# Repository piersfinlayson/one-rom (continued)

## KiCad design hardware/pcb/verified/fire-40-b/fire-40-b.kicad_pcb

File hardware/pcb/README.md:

# PCB Files

Contains One ROM PCB design files, organised into:

- [`verified/`](verified/README.md) - Verified designs that have been tested and work.
- [`unverified/`](unverified/README.md) - Unverified designs that have not been tested.
- [`3dmodels/`](3dmodels/) - 3D models of parts with no standard kicad model of their own.
- [`scripts/`](scripts/) - Scripts that build models and render the PCBs.

Before using any of the designs, review the hardware [LICENSE](/LICENSE.md#cern-ohl-w-20-license) and [NOTICE](/hardware/NOTICE) files.

## Recommended Revisions

Last Updated 8th September 2026.

The following table lists the recommended verified designs.  Each design has been manufactured and assembled using JLCPCB's PCB assembly service, and verified to work correctly.

| Model | MCU | Pins | USB | SWD | Image Select Pins | X Pins | RGB | PCB |
|-------|-----|------|-----|-----|-------------------|--------|-----|-------|
| Fire  | RP2354A | 24 | C | ✓ | 4 | 2 | ✓ | [fire-24-f](./verified/fire-24-f/README.md) |
| Fire  | RP2354A | 24 | C (upright) | ✓ | 4 | 2 | ✓ | [fire-24-g](./verified/fire-24-g/README.md) |
| Fire  | RP2354B | 28 | C | ✓ | 4 | 2 | ✓ | [fire-28-c](./verified/fire-28-c/README.md) |
| Fire  | RP2354B | 28 | C (upright) | ✓ | 4 | 2 | ✓ | [fire-28-d](./verified/fire-28-d/README.md) |
| Fire  | RP2354B | 32 | C | ✓ | 4 | n/a | ✓ | [fire-32-b2](./verified/fire-32-b2/README.md) |
| Fire  | RP2354B | 32 | C (upright) | ✓ | 4 | n/a | ✓ | [fire-32-c](./verified/fire-32-c/README.md) |
| Fire  | RP2354B | 40 | C | ✓ | 4 | n/a | ✓ | [fire-40-b](./verified/fire-40-b/README.md) |
| Fire  | RP2354B | 40 | C (upright) | ✓ | 4 | n/a | ✓ | [fire-40-c](./verified/fire-40-c/README.md) |

**One ROM 28C onwards, 32 and 40 require components on the top and bottom of the PCB**

To identify a board or see it looks like see [onerom.org/identify/](https://onerom.org/identify/).

There may be later, unverified, revisions not in the list above.  These may have improvements over the recommended revisions, but they have not been verified to work.  If you want to use one of these later revisions, read the relevant README before ordering.

## Alternative Components

Sometimes your PCB manufacturer/assembler may be out of stock of a particular component.  This section lists some reasonable alternatives, using LCSC/JLC part numbers.

| Original Component | Original LCSC/JLC Part Number | Alternative Component | Alternative LCSC/JLC Part Number | Verified? | Notes |
|-|-|-|-|-|-|
| Diodes Inc AP2112K-3.3TRG1 | C51118 | Tech Public AP2112K-3.3TRG1 | C23380830 | Yes | Jelly bean part, same specs |
| Uniroyal 0201WMF1002TEE | C473048 | Yageo RC0201FR-0710KL | C106225 | No | Jelly bean part, same specs |
| Samsung CL03A104KO3NNNC | C307380 | Murata GRM033Z71C104KE14D | C668346 | Yes | 0.1uF decoupler.  X7R rather than X5R - this is the part used on all boards fabbed to date. |

The RP2354B can be replaced with the RP2350B _if the design supports external flash and it is populated with the correct resistors present/missing_.

Some designs, such as fire-40-c, have hardware support for both external flash plus an RP2354B, so two lots of flash.  Fabricating this option requires the correct 0R resistors to be populated/not populated.  See the board schematic for more details.

**The external flash option has not been tested on the current recommended designs.**

In some cases, alternative BOM/POS files are already provided for some alternative components.  In other cases, you may need to edit the BOM/POS files yourself to substitute the alternative component.  _Always_ double check component values, part numbers and placement before ordering.

## Notes on Fabrication

All recommended designs have been manufactured and assembled using JLCPCB's PCB assembly service.  The gerbers and BOM/POS files in each revision's `fab/` directory are compatible with JLCPCB's requirements.

Some variants offer multiple sets of BOM/POS files or different combinations of components.  Read the relevant revision's README for details.

You need to exercise care when submitting the order to ensure the correct options are selected.  In particular:

- Select economic assembly, not standard assembly, for cost reasons, if available for your choice of board.
- Use standard 1.6mm PCB thickness.  You probably want HASL with lead finish for cost reasons.
- You have to select the desired PCB colour as part of the PCB ordering process.  Red is recommended for Fire and blue for Ice.
- As of late 2025 you no longer need to remove JLC's order ID from the PCBs, but it is worth checking this is still the case when you place your order.
- When selecting assembly choose either top or top + bottom depending on whether your chosen design has parts on the bottom.
- After uploading the BOM and position files for assembly, you need to ensure all parts are available and checked.
- You must ensure JLC is showing the correct orientation for all components.  There are silkscreen markings for pin 1 on all ICs and polarized components - ensure this matches the pink dot of the component in the viewer.  Also ensure the USB connector is the correct orientation.
- ** Make sure you check the bottom if components are supposed to be there. **

Occasionally, some chosen parts are out of stock on JLCPCB.  One ROM has been designed with extremely common parts where possible, which JLC tend to hold large stocks of.  However, if a part is unavailable you may need to select an alternative part.  Ensure the alternative part has the same footprint and electrical characteristics (e.g. capacitance, voltage rating, etc) as the original part.  If in doubt, query within github discussions for advice. 

JLC may raise an issue with you after submitting your order.  Common issues include:
- JLC may ask to add side rails with stamp holes, to help with the PCB assembly process.  While One ROM has been successfully fabbed without these, if JLC recommends them it is best to accept this change, as otherwise they may not warrant the assembled boards.  The side rails can be snapped off using the "mouse bites" (stamp holes) after assembly.  JLC may or may not accept replacing stamp holes with v-score - as v-score is not available on their economic service.

If in doubt, query within github discussions for advice.

Assembly errors:
- Ice boards have rarely, if ever, experienced assembly errors.
- The first few batches of Fire boards experienced some assembly issues, particularly with respect to the RP2350 MCU solder pad fillets.  More recent boards and orders have been without issue.  It is unclear whether differences in the later PCBs or improvements in JLC's assembly process are responsible for this improvement.  If you do experience assembly issues, raise with JLC support.  It would also be interesting to hear on github discussions what issues you experienced, so others can be aware.

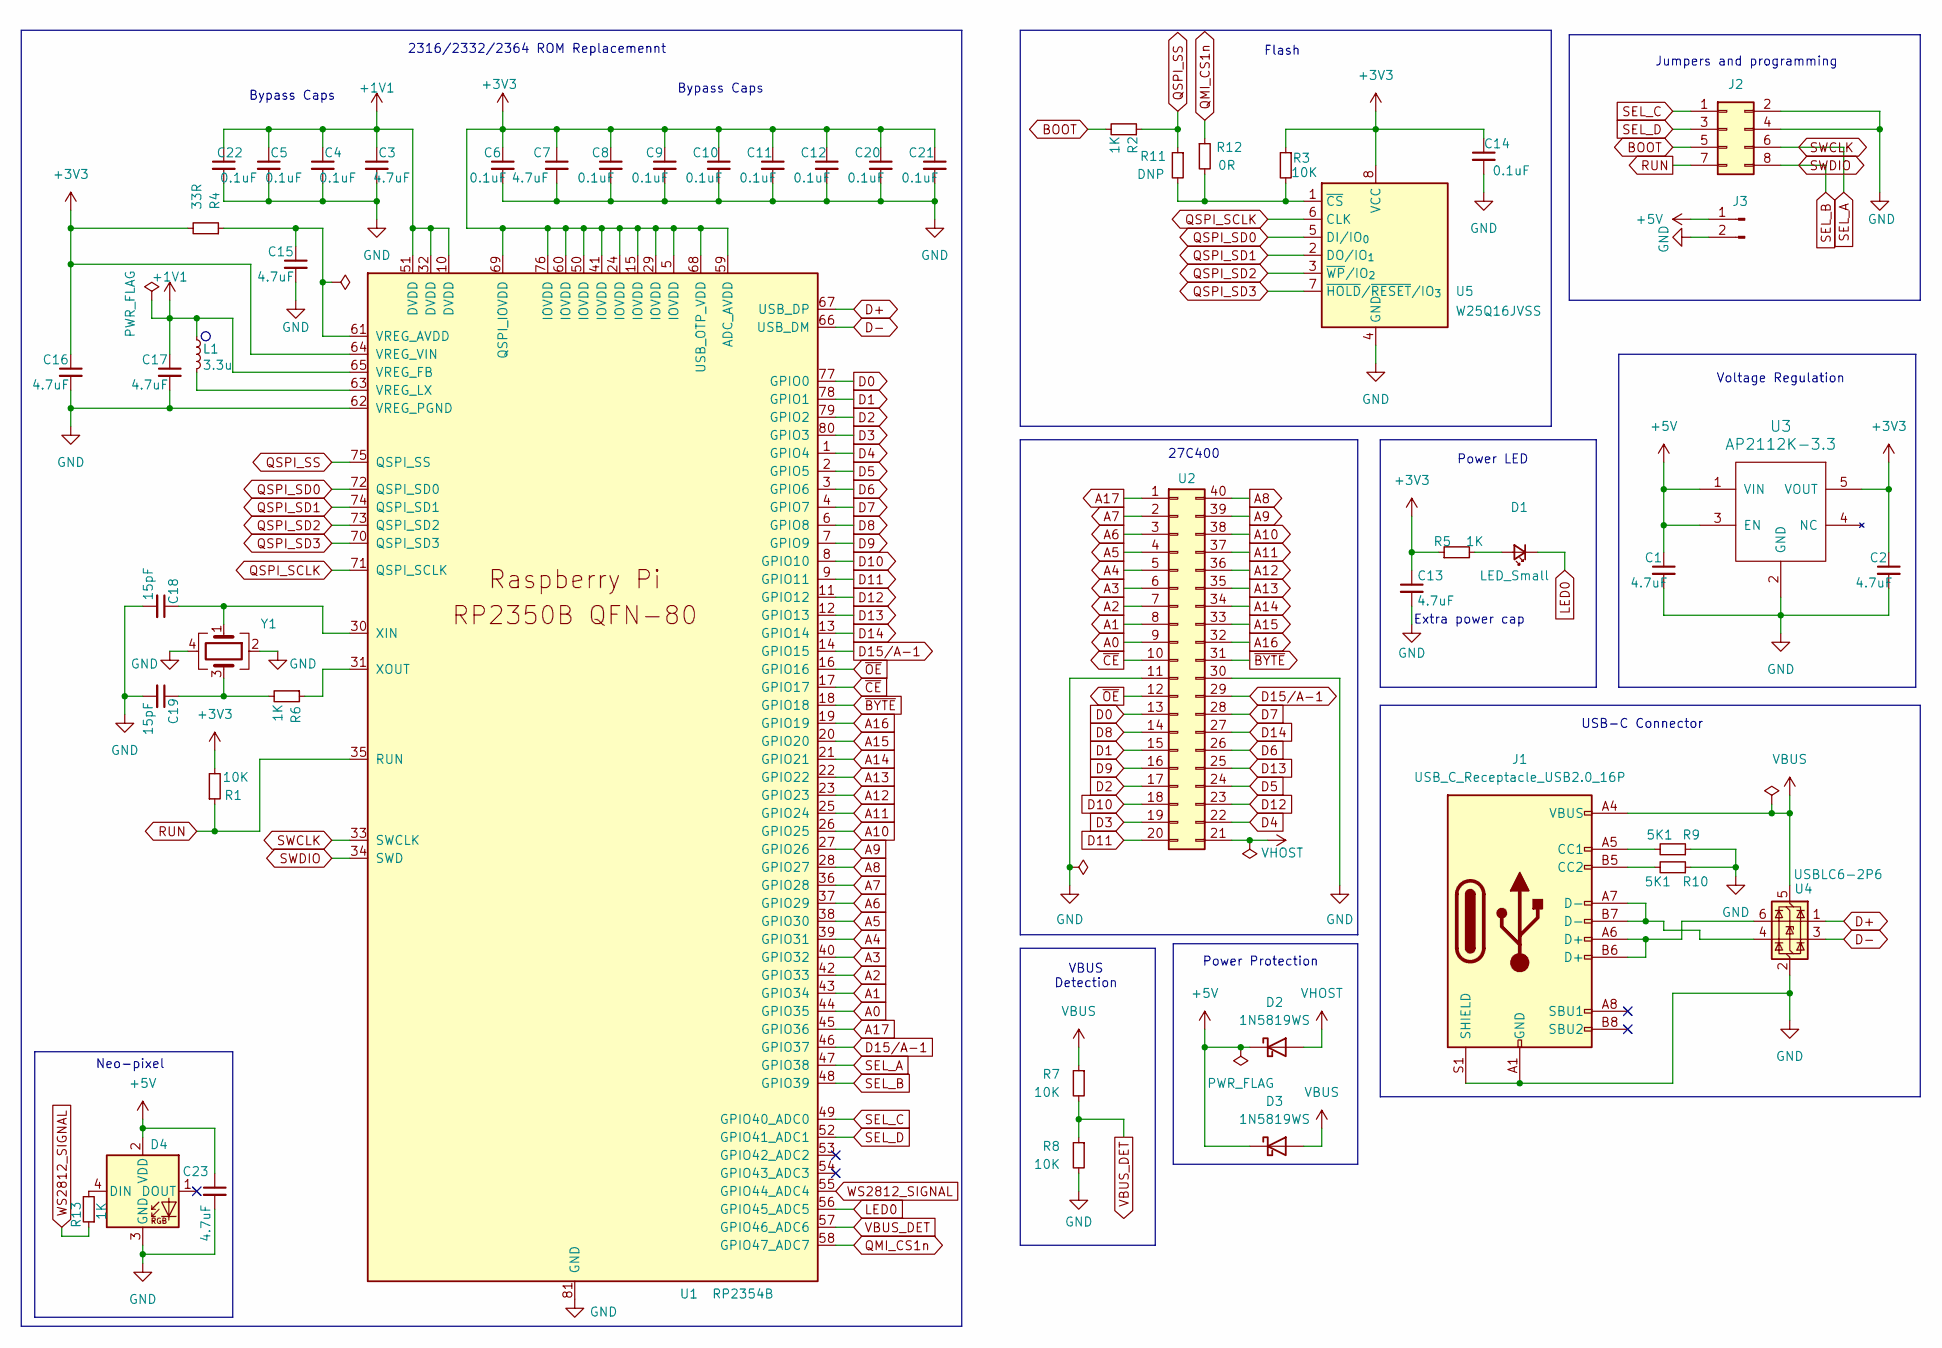
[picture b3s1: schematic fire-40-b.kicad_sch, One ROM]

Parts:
C1, C2, C3, C7, C13, C15, C23: 4.7uF; C_0402_1005Metric; LCSC C23733
C4, C5, C6, C8, C9, C10, C11, C12, C14, C20, C21, C22: 0.1uF; C_0402_1005Metric; LCSC C1525
C16, C17: 4.7uF; C_0402_1005Metric_small_pads; LCSC C23733
C18, C19: 15pF; C_0402_1005Metric; LCSC C1548
D1: LED_Small; LED_0603_1608Metric; LCSC C2286
D2, D3: 1N5819WS; D_SOD-323; LCSC C191023
D4: XL-1010RGBC-WS2812B; XL-1010RGBC-2812B; LCSC C5349953
J1: USB_C_Receptacle_USB2.0_16P; USB_C_connector_c2765186; LCSC C2765186
J2: Conn_02x04_Odd_Even; PinHeader_2x04_P2.54mm_Vertical custom silkscreen
J3: Conn_01x02_Pin; PinHeader_1x02_P2.54mm_Vertical
L1: 3.3u; L_pol_2016; LCSC C42411119
R1, R3, R7, R8: 10K; R_0402_1005Metric; LCSC C25744
R2, R5, R6, R13: 1K; R_0402_1005Metric; LCSC C11702
R4: 33R; R_0402_1005Metric; LCSC C25105
R9, R10: 5K1; R_0402_1005Metric; LCSC C25905
R11: DNP; R_0402_1005Metric; LCSC C17168
R12: 0R; R_0402_1005Metric; LCSC C17168
U1: RP2354B; RP2350-QFN-80-1EP_10x10_P0.4mm_EP3.4x3.4mm_ThermalVias; LCSC C39843328
U2: Conn_02x20_Counter_Clockwise; 2x20 dip pin output 600mil centres
U3: AP2112K-3.3; SOT-23-5; LCSC C51118
U4: USBLC6-2P6; SOT-666; LCSC C15999
U5: W25Q16JVSS; Winbond_USON-8-1EP_3x2mm_P0.5mm_EP0.2x1.6mm; LCSC C2843335
Y1: Crystal_GND24; Crystal_SMD_Abracon_ABM8G-4Pin_3.2x2.5mm; LCSC C20625731

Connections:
+1V1: C3.1, C4.1, C5.1, C17.1, C22.1, L1.1, U1.10 (DVDD), U1.32 (DVDD), U1.51 (DVDD), U1.65 (VREG_FB)
+3V3: C2.1, C6.1, C7.1, C8.1, C9.1, C10.1, C11.1, C12.1, C13.1, C14.1, C16.1, C20.1, C21.1, R1.2, R3.1, R4.2, R5.1, U1.5 (IOVDD), U1.15 (IOVDD), U1.24 (IOVDD), U1.29 (IOVDD), U1.41 (IOVDD), U1.50 (IOVDD), U1.59 (ADC_AVDD), U1.60 (IOVDD), U1.64 (VREG_VIN), U1.68 (USB_OTP_VDD), U1.69 (QSPI_IOVDD), U1.76 (IOVDD), U3.5 (VOUT), U5.8 (VCC)
+5V: C1.1, C23.1, D2.1 (K), D3.1 (K), D4.2 (VDD), J3.1, U3.1 (VIN), U3.3 (EN)
A0: U1.44 (GPIO35), U2.9
A1: U1.43 (GPIO34), U2.8
A2: U1.42 (GPIO33), U2.7
A3: U1.40 (GPIO32), U2.6
A4: U1.39 (GPIO31), U2.5
A5: U1.38 (GPIO30), U2.4
A6: U1.37 (GPIO29), U2.3
A7: U1.36 (GPIO28), U2.2
A8: U1.28 (GPIO27), U2.40
A9: U1.27 (GPIO26), U2.39
A10: U1.26 (GPIO25), U2.38
A11: U1.25 (GPIO24), U2.37
A12: U1.23 (GPIO23), U2.36
A13: U1.22 (GPIO22), U2.35
A14: U1.21 (GPIO21), U2.34
A15: U1.20 (GPIO20), U2.33
A16: U1.19 (GPIO19), U2.32
A17: U1.45 (GPIO36), U2.1
BOOT: J2.5, R2.2
D0: U1.77 (GPIO0), U2.13
D1: U1.78 (GPIO1), U2.15
D2: U1.79 (GPIO2), U2.17
D3: U1.80 (GPIO3), U2.19
D4: U1.1 (GPIO4), U2.22
D5: U1.2 (GPIO5), U2.24
D6: U1.3 (GPIO6), U2.26
D7: U1.4 (GPIO7), U2.28
D8: U1.6 (GPIO8), U2.14
D9: U1.7 (GPIO9), U2.16
D10: U1.8 (GPIO10), U2.18
D11: U1.9 (GPIO11), U2.20
D12: U1.11 (GPIO12), U2.23
D13: U1.12 (GPIO13), U2.25
D14: U1.13 (GPIO14), U2.27
D15/A-1: U1.14 (GPIO15), U1.46 (GPIO37), U2.29
D+: U1.67 (USB_DP), U4.1 (I/O1)
D-: U1.66 (USB_DM), U4.3 (I/O2)
GND: C1.2, C2.2, C3.2, C4.2, C5.2, C6.2, C7.2, C8.2, C9.2, C10.2, C11.2, C12.2, C13.2, C14.2, C15.2, C16.2, C17.2, C18.2, C19.2, C20.2, C21.2, C22.2, C23.2, D4.3 (GND), J1.A1 (GND), J1.A12 (GND), J1.B1 (GND), J1.B12 (GND), J1.S1 (SHIELD), J2.2, J2.4, J3.2, R8.2, R9.1, R10.1, U1.62 (VREG_PGND), U1.81 (GND), U2.11, U2.30, U3.2 (GND), U4.2 (GND), U5.4 (GND), Y1.2, Y1.4
LED0: D1.1 (K), U1.56 (GPIO45_ADC5)
unnamed: C19.1, R6.2, Y1.3
unnamed: D1.2 (A), R5.2
unnamed: D4.4 (DIN), R13.2
unnamed: J1.A5 (CC1), R9.2
unnamed: J1.B5 (CC2), R10.2
unnamed: J1.A6 (D+), J1.B6 (D+), U4.6 (I/O1)
unnamed: J1.A7 (D-), J1.B7 (D-), U4.4 (I/O2)
unnamed: C15.1, R4.1, U1.61 (VREG_AVDD)
unnamed: L1.2, U1.63 (VREG_LX)
unnamed: C18.1, U1.30 (XIN), Y1.1
unnamed: R6.1, U1.31 (XOUT)
unnamed: R3.2, R11.2, R12.2, U5.1 (~CS)
QMI_CS1n: R12.1, U1.58 (GPIO47_ADC7)
QSPI_SCLK: U1.71 (QSPI_SCLK), U5.6 (CLK)
QSPI_SD0: U1.72 (QSPI_SD0), U5.5 (DI/IO_{0})
QSPI_SD1: U1.74 (QSPI_SD1), U5.2 (DO/IO_{1})
QSPI_SD2: U1.73 (QSPI_SD2), U5.3 (~WP/IO_{2})
QSPI_SD3: U1.70 (QSPI_SD3), U5.7 (~HOLD/~RESET/IO_{3})
QSPI_SS: R2.1, R11.1, U1.75 (QSPI_SS)
RUN: J2.7, R1.1, U1.35 (RUN)
SEL_A: J2.6, U1.33 (SWCLK), U1.47 (GPIO38)
SEL_B: J2.8, U1.34 (SWD), U1.48 (GPIO39)
SEL_C: J2.1, U1.49 (GPIO40_ADC0)
SEL_D: J2.3, U1.52 (GPIO41_ADC1)
VBUS: D3.2 (A), J1.A4 (VBUS), J1.A9 (VBUS), J1.B4 (VBUS), J1.B9 (VBUS), R7.1, U4.5 (VBUS)
VBUS_DET: R7.2, R8.1, U1.57 (GPIO46_ADC6)
VHOST: D2.2 (A), U2.21
WS2812_SIGNAL: R13.1, U1.55 (GPIO44_ADC4)
~BYTE: U1.18 (GPIO18), U2.31
~CE: U1.17 (GPIO17), U2.10
~OE: U1.16 (GPIO16), U2.12

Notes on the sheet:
USB-C Connector
Voltage Regulation
Neo-pixel
Extra power cap
2316/2332/2364 ROM Replacemennt
Bypass Caps
Power LED
Power Protection
27C400
VBUS Detection
Flash
Jumpers and programming

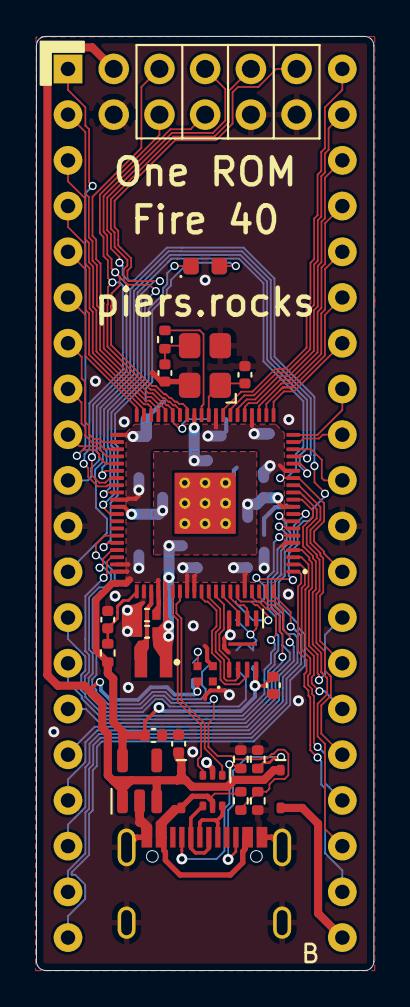
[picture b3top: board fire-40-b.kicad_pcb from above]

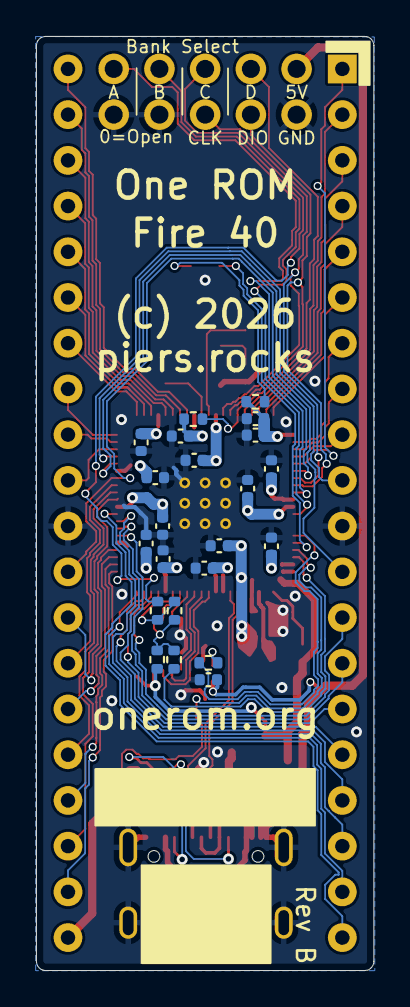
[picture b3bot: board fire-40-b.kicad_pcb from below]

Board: 2 copper layers, 18.7 x 51.9 mm, 50 parts (22 on the bottom side), 73 nets.

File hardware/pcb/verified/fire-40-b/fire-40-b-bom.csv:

"Reference","Qty","Value","DNP","Exclude from BOM","Exclude from Board","Footprint","Datasheet","LCSC"
"C1,C2,C3,C7,C13,C15,C23,C16,C17","9","4.7uF","","","","Capacitor_SMD:C_0402_1005Metric","~","C23733"
"C4,C5,C6,C8,C9,C10,C11,C12,C14,C20,C21,C22","12","0.1uF","","","","Capacitor_SMD:C_0402_1005Metric","~","C1525"
"C18,C19","2","15pF","","","","Capacitor_SMD:C_0402_1005Metric","~","C1548"
"D1","1","LED_Small","","","","LED_SMD:LED_0603_1608Metric","~","C2286"
"D2,D3","2","1N5819WS","","","","Diode_SMD:D_SOD-323","","C191023"
"D4","1","XL-1010RGBC-WS2812B","","","","piers retro:XL-1010RGBC-2812B","https://jlcpcb.com/partdetail/XINGLIGHT-XL_1010RGBC2812B/C5349953","C5349953"
"J1","1","USB_C_Receptacle_USB2.0_16P","","","","piers retro footprints:USB_C_connector_c2765186","https://www.usb.org/sites/default/files/documents/usb_type-c.zip","C2765186"
"L1","1","3.3u","","","","RP2350_60QFN_minimal:L_pol_2016","~","C42411119"
"R1,R3,R7,R8","4","10K","","","","Resistor_SMD:R_0402_1005Metric","~","C25744"
"R2,R5,R6,R13","4","1K","","","","Resistor_SMD:R_0402_1005Metric","~","C11702"
"R4","1","33R","","","","Resistor_SMD:R_0402_1005Metric","~","C25105"
"R9,R10","2","5K1","","","","Resistor_SMD:R_0402_1005Metric","~","C25905"
"R12","1","0R","","","","Resistor_SMD:R_0402_1005Metric","~","C17168"
"U1","1","RP2354B","","","","RP2350B:RP2350-QFN-80-1EP_10x10_P0.4mm_EP3.4x3.4mm_ThermalVias",""," C39843328"
"U3","1","AP2112K-3.3","","","","Package_TO_SOT_SMD:SOT-23-5","","C51118"
"U4","1","USBLC6-2P6","","","","Package_TO_SOT_SMD:SOT-666","https://www.st.com/resource/en/datasheet/usblc6-2.pdf","C15999"
"Y1","1","Crystal_GND24","","","","Crystal:Crystal_SMD_Abracon_ABM8G-4Pin_3.2x2.5mm","~","C20625731"

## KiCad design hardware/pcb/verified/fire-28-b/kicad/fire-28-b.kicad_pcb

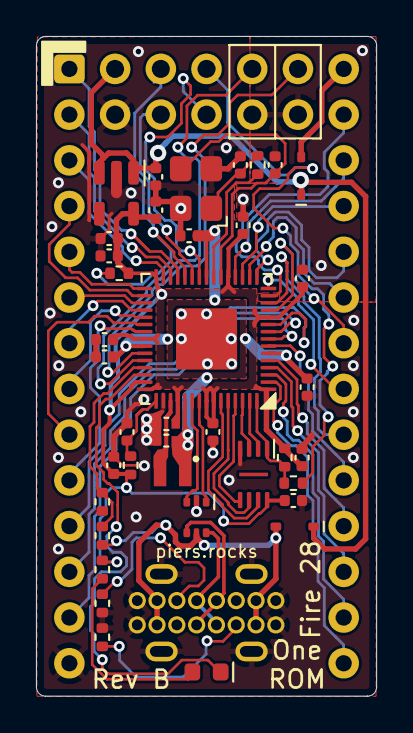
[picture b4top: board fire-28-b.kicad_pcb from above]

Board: 2 copper layers, 18.9 x 36.7 mm, 42 parts (0 on the bottom side), 58 nets.

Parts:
C1, C2, C3, C7, C13, C15: 4.7uF; C_0402_1005Metric
C4, C5, C6, C8, C9, C10, C11, C12, C14: 0.1uF; C_0402_1005Metric
C16, C17: 4.7uF; C_0402_1005Metric_small_pads
C18, C19: 15pF; C_0402_1005Metric
D1: LED_Small; LED_0603_1608Metric
D2, D3: 1N5819WS; D_SOD-323
J1: MC-118LD-H65; USB-C-upright-C6332304-hanbo-MC-118LD-H65
J2: Conn_02x04_Odd_Even; PinHeader_2x04_P2.54mm_Vertical custom silkscreen
J3: Conn_01x02_Pin; PinHeader_1x02_P2.54mm_Vertical
L1: 3.3u; L_pol_2016
R1, R3, R7, R8: 10K; R_0402_1005Metric
R2, R5, R6: 1K; R_0402_1005Metric
R4: 33R; R_0402_1005Metric
R9, R10: 5K1; R_0402_1005Metric
U1: RP2350_60QFN; RP2350-QFN-60-1EP_7x7_P0.4mm_EP3.4x3.4mm_ThermalVias
U2: 28 Pin ROM; 28 pin rom footprint
U3: AP2112K-3.3; SOT-23-5
U4: USBLC6-2P6; SOT-666
U5: W25Q16JVSS; Winbond_USON-8-1EP_3x2mm_P0.5mm_EP0.2x1.6mm
Y1: Crystal_GND24; Crystal_SMD_Abracon_ABM8G-4Pin_3.2x2.5mm

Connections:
+1V1: C3.1, C4.1, C5.1, C17.1, L1.1, U1.6 (DVDD), U1.23 (DVDD), U1.39 (DVDD), U1.50 (VREG_FB)
+3V3: C2.1, C6.1, C7.1, C8.1, C9.1, C10.1, C11.1, C12.1, C13.1, C14.1, C16.1, R1.2, R3.1, R4.2, R5.1, U1.1 (IOVDD), U1.11 (IOVDD), U1.20 (IOVDD), U1.30 (IOVDD), U1.38 (IOVDD), U1.44 (ADC_AVDD), U1.45 (IOVDD), U1.49 (VREG_VIN), U1.53 (USB_OTP_VDD), U1.54 (QSPI_IOVDD), U3.5 (VOUT), U5.8 (VCC)
+5V: C1.1, D2.1 (K), D3.1 (K), J3.1, U3.1 (VIN), U3.3 (EN)
A0: U1.37 (GPIO25), U2.10 (A0)
A1: U1.36 (GPIO24), U2.9 (A1)
A2: U1.35 (GPIO23), U2.8 (A2)
A3: U1.34 (GPIO22), U2.7 (A3)
A4: U1.33 (GPIO21), U2.6 (A4)
A5: U1.31 (GPIO19), U2.5 (A5)
A6: U1.32 (GPIO20), U2.4 (A6)
A7: U1.29 (GPIO18), U2.3 (A7)
A8: U1.18 (GPIO14), U2.25 (A8)
A9: U1.16 (GPIO12), U2.24 (A9)
A10: U1.15 (GPIO11), U2.21 (A10)
A11: U1.17 (GPIO13), U2.23 (A11)
A12: U1.28 (GPIO17), U2.2 (A12)
A13: U1.19 (GPIO15), U2.26 (A13)
A15: U1.27 (GPIO16), U2.1 (A15)
BOOT: J2.5, R2.2
CS3/A14: U1.14 (GPIO10), U2.27 (A14)
D0: U1.10 (GPIO7), U2.11 (D0)
D1: U1.9 (GPIO6), U2.12 (D1)
D2: U1.8 (GPIO5), U2.13 (D2)
D3: U1.2 (GPIO0), U2.15 (D3)
D4: U1.3 (GPIO1), U2.16 (D4)
D5: U1.4 (GPIO2), U2.17 (D5)
D6: U1.5 (GPIO3), U2.18 (D6)
D7: U1.7 (GPIO4), U2.19 (D7)
D+: U1.52 (USB_DP), U4.1 (I/O1)
D-: U1.51 (USB_DM), U4.3 (I/O2)
GND: C1.2, C2.2, C3.2, C4.2, C5.2, C6.2, C7.2, C8.2, C9.2, C10.2, C11.2, C12.2, C13.2, C14.2, C15.2, C16.2, C17.2, C18.2, C19.2, J1.A1 (GND), J1.A12 (GND), J1.B1 (GND), J1.B12 (GND), J1.S1 (SHIELD), J2.2, J2.4, J3.2, R8.2, R9.1, R10.1, U1.47 (VREG_PGND), U1.61 (GND), U2.14 (GND), U3.2 (GND), U4.2 (GND), U5.4 (GND), Y1.2, Y1.4
LED0: D1.1 (K), U1.43 (GPIO29_ADC3)
unnamed: C19.1, R6.2, Y1.1
unnamed: D1.2 (A), R5.2
unnamed: J1.A5 (CC1), R9.2
unnamed: J1.B5 (CC2), R10.2
unnamed: J1.A6 (D+), J1.B6 (D+), U4.6 (I/O1)
unnamed: J1.A7 (D-), J1.B7 (D-), U4.4 (I/O2)
unnamed: C15.1, R4.1, U1.46 (VREG_AVDD)
unnamed: L1.2, U1.48 (VREG_LX)
unnamed: C18.1, U1.21 (XIN), Y1.3
unnamed: R6.1, U1.22 (XOUT)
QSPI_SCLK: U1.56 (QSPI_SCLK), U5.6 (CLK)
QSPI_SD0: U1.57 (QSPI_SD0), U5.5 (DI/IO_{0})
QSPI_SD1: U1.59 (QSPI_SD1), U5.2 (DO/IO_{1})
QSPI_SD2: U1.58 (QSPI_SD2), U5.3 (~WP/IO_{2})
QSPI_SD3: U1.55 (QSPI_SD3), U5.7 (~HOLD/~RESET/IO_{3})
QSPI_SS: R2.1, R3.2, U1.60 (QSPI_SS), U5.1 (~CS)
RUN: J2.7, R1.1, U1.26 (RUN)
SEL_A: J2.1, U1.40 (GPIO26_ADC0)
SEL_B: J2.3, U1.41 (GPIO27_ADC1)
SWCLK: J2.6, U1.24 (SWCLK)
SWDIO: J2.8, U1.25 (SWD)
VBUS: D3.2 (A), J1.A4 (VBUS), J1.A9 (VBUS), J1.B4 (VBUS), J1.B9 (VBUS), R7.1, U4.5 (VBUS)
VBUS_DET: R7.2, R8.1, U1.42 (GPIO28_ADC2)
VHOST: D2.2 (A), U2.28 (VCC)
~CE: U1.13 (GPIO9), U2.20 (~CE)
~OE: U1.12 (GPIO8), U2.22 (~OE)

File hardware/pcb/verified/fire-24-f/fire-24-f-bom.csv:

"Reference","Qty","Value","DNP","Exclude from BOM","Exclude from Board","Footprint","Datasheet","LCSC"
"C1,C2,C7,C13,C15,C16,C17","7","4.7uF","","","","Capacitor_SMD:C_0402_1005Metric","~","C23733"
"C3,C4,C5,C6,C8,C9,C10,C11,C12,C14","10","0.1uF","","","","Capacitor_SMD:C_0201_0603Metric","~","C668346"
"C18,C19","2","15pF","","","","Capacitor_SMD:C_0201_0603Metric","~","C85891"
"D1","1","LED_Small","","","","LED_SMD:LED_0402_1005Metric","~","C25503345"
"D2,D3","2","1N5819WS","","","","Diode_SMD:D_SOD-323","","C191023"
"D4","1","XL-1010RGBC-WS2812B","","","","piers retro:XL-1010RGBC-2812B","https://jlcpcb.com/partdetail/XINGLIGHT-XL_1010RGBC2812B/C5349953","C5349953 "
"J4","1","USB_C_Receptacle_USB2.0_16P","","","","piers retro:USB_C_connector_c2765186","https://www.usb.org/sites/default/files/documents/usb_type-c.zip","C2765186"
"L1","1","3.3u","","","","RP2350_60QFN_minimal:L_pol_2016","~","C42411119"
"R1,R3,R7,R8","4","10K","","","","Resistor_SMD:R_0201_0603Metric","~","C473048"
"R2,R5,R6,R11","4","1K","","","","Resistor_SMD:R_0201_0603Metric","~","C270365"
"R4","1","33R","","","","Resistor_SMD:R_0402_1005Metric","~","C25105"
"R9,R10","2","5K1","","","","Resistor_SMD:R_0201_0603Metric","~","C270344"
"U1","1","RP2350_60QFN","","","","RP2350_60QFN_minimal:RP2350-QFN-60-1EP_7x7_P0.4mm_EP3.4x3.4mm_ThermalVias",""," C41378174"
"U3","1","AP2112K-3.3","","","","Package_TO_SOT_SMD:SOT-23-5","","C51118"
"U4","1","USBLC6-2P6","","","","Package_TO_SOT_SMD:SOT-666","https://www.st.com/resource/en/datasheet/usblc6-2.pdf","C15999"
"Y1","1","Crystal_GND24","","","","Crystal:Crystal_SMD_Abracon_ABM8G-4Pin_3.2x2.5mm","~","C20625731"

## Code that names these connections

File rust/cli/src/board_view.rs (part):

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// ROM socket
// ===========================================================================

/// The GPIO(s) behind a socket pin, formatted (e.g. `GPIO16` or `GPIO16/GPIO40`),
/// or `None` if the pin maps to no GPIO (a power / not-connected pin).
fn socket_gpios(board: &Board, pin: u8) -> Option<String> {
    let gpios = board.gpios_for_socket_pin(pin);
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    #[test]
    fn pin_header_flags_adc_select_pins() {
        let s = render_pin_header(&board()).expect("fire-24-f has a header");
        // SEL_A/SEL_B sit behind the RP2350A ADC pins GPIO26/27 → 3.3V-only.
        assert!(s.contains("SEL_A"));
        assert!(s.contains("GPIO26"));
        assert!(s.contains("!!3V3!!"));
        // SEL_C/SEL_D (GPIO25/24) are the SWD-muxed, 5V-tolerant pair.
        assert!(s.contains("SWDIO"));
        assert!(s.contains("GPIO24"));
        assert!(s.contains("5V = 5V-tolerant"));
        // X pins appear on the third row.
        assert!(s.contains("X1"));
        assert!(s.contains("GPIO9"));
    }

    #[test]
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    #[test]
    fn socket_gpio_map_has_no_functions() {
        let s = render_rom_socket(&board(), None, false);
        assert!(s.contains("GPIO16"));
        assert!(s.contains("GPIO map"));
        // Power pins still labelled from the board's accepted chip types.
        assert!(s.contains("VCC"));
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    fn socket_function_with_gpio_overlays_both() {
        let s = render_rom_socket(&board(), Some(ChipType::Chip2364), true);
        assert!(s.contains("with GPIOs"));
        assert!(s.contains("A7 (GPIO16)"));
        assert!(s.contains("CS1 (GPIO10)"));
    }

    #[test]
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        // header breaks out high address lines on the third row.
        let b = Board::try_from_str("fire-32-b").unwrap();
        let s = render_pin_header(&b).expect("fire-32-b has a header");
        // SEL_A/SEL_B behind GPIO40/41 (RP235xB ADC) are flagged 3.3V-only.
        assert!(s.contains("GPIO40"));
        assert!(s.contains("!!3V3!!"));
        // Address lines, not X pins, on the third row → the addr legend, not X.
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
    #[test]
    fn socket_27c400_is_16bit_with_byte_pin() {
        // 27C400 is a 40-pin 16-bit EPROM: D0-D15, a /BYTE pin, and CE/OE.
        let b = Board::try_from_str("fire-40-b").unwrap();
        let s = render_rom_socket(&b, Some(ChipType::Chip27C400), false);
        assert!(s.contains("D15"));
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
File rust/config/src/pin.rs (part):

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
//! MCU GPIOs and header pins.
//!
//! A pin is written as an MCU GPIO (`gpio23`) or a header pin (`sel_a`,
//! `x1`). The CLI's `--pin` and the config key `reserved_pins` use this syntax.
//!
//! ## Parsing and resolution are separate steps
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#[derive(Debug, Clone, Copy, PartialEq, Eq)]
#[non_exhaustive]
pub enum HeaderPin {
    /// An image select pin, indexed from 0 for `sel_a`.
    Select(u8),
    /// The X1 pin.
    X1,
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            .filter(|pin| pin.gpio_on(board).is_some())
    }

    /// The pin's silkscreen label, for example `SEL_A`.
    ///
    /// [`Display`](fmt::Display) writes the form a user types, for example
    /// `sel_a`.
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            type Value = Pin;

            fn expecting(&self, f: &mut fmt::Formatter<'_>) -> fmt::Result {
                f.write_str("a header pin, for example 'sel_a' or 'x1'")
            }

            fn visit_str<E>(self, v: &str) -> Result<Pin, E>
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}

impl fmt::Display for ResolvedPin {
    /// `gpio9` for a GPIO, `sel_a (gpio9)` for a header pin.
    fn fmt(&self, f: &mut fmt::Formatter<'_>) -> fmt::Result {
        match self.pin {
            Pin::Gpio(gpio) => write!(f, "gpio{gpio}"),
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    BareNumber,
    /// An address line, for example `a17`.
    AddressLine,
    /// A dedicated MCU pin that isn't a GPIO, for example `run`.
    NotAGpio,
    /// Anything else.
    Unrecognised,
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        f.write_str(match self {
            PinError::Empty => "no pin given",
            PinError::MissingGpioNumber => {
                "'gpio' must be followed by a GPIO number, for example 'gpio23'"
            }
            PinError::GpioOutOfRange => "GPIO numbers are 0 to 255",
            PinError::BareNumber => {
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
    #[test]
    fn gpio_names_parse() {
        assert_eq!(parse_pin("gpio0"), Ok(Pin::Gpio(0)));
        assert_eq!(parse_pin("gpio23"), Ok(Pin::Gpio(23)));
        assert_eq!(parse_pin("gpio047"), Ok(Pin::Gpio(47)));
        assert_eq!(parse_pin("gpio255"), Ok(Pin::Gpio(255)));
        assert_eq!(parse_pin("GPIO23"), Ok(Pin::Gpio(23)));
        assert_eq!(parse_pin("  Gpio23  "), Ok(Pin::Gpio(23)));
    }

    #[test]
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            ("23", PinError::BareNumber),
            ("a0", PinError::AddressLine),
            ("A17", PinError::AddressLine),
            ("run", PinError::NotAGpio),
            ("BootSel", PinError::NotAGpio),
            ("swdio", PinError::NotAGpio),
            ("a", PinError::Unrecognised),
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
    #[test]
    fn a_pin_displays_as_it_is_typed() {
        assert_eq!(Pin::Gpio(23).to_string(), "gpio23");
        assert_eq!(Pin::Header(HeaderPin::Select(0)).to_string(), "sel_a");
        assert_eq!(Pin::Header(HeaderPin::Select(6)).to_string(), "sel_g");
        assert_eq!(Pin::Header(HeaderPin::X1).to_string(), "x1");
        assert_eq!(HeaderPin::X2.to_string(), "x2");
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
    #[test]
    fn a_pin_has_a_silkscreen_name() {
        assert_eq!(HeaderPin::Select(2).silkscreen().to_string(), "SEL_C");
        assert_eq!(HeaderPin::X1.silkscreen().to_string(), "X1");
        assert_eq!(HeaderPin::X2.silkscreen().to_string(), "X2");
    }
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            })
        );
        assert_eq!(
            parse_pin("sel_c")
                .unwrap()
                .resolve(Some(&board("fire-28-a"))),
            Err(ResolveError::NoSuchPin {
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            Err(ResolveError::NoBoard { pin: HeaderPin::X1 })
        );
        // A GPIO resolves without a board.
        let gpio = parse_pin("gpio23").unwrap().resolve(None).unwrap();
        assert_eq!((gpio.gpio(), gpio.pin()), (23, Pin::Gpio(23)));
    }

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    fn a_resolved_pin_shows_both_names() {
        let b = board("fire-24-f");
        let pin = parse_pin("x1").unwrap().resolve(Some(&b)).unwrap();
        assert_eq!(pin.to_string(), "x1 (gpio9)");
        assert_eq!(pin.pin(), Pin::Header(HeaderPin::X1));
    }

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
    #[test]
    fn a_pin_round_trips_through_serde() {
        let pins: Vec<Pin> = serde_json::from_str(r#"["SEL-C", " x1 ", "GPIO25"]"#).unwrap();
        assert_eq!(
            pins,
            [
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        );
        assert_eq!(
            serde_json::to_string(&pins).unwrap(),
            r#"["sel_c","x1","gpio25"]"#
        );
        let error = serde_json::from_str::<Pin>(r#""a17""#).unwrap_err();
        assert!(error.to_string().contains("'a17'"), "{error}");
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        let b = board("fire-24-f");
        let before = counting::allocations();
        for spec in [
            "sel_c", "SEL-G", "x1", "gpio25", "", "gpio", "gpio999", "23", "a17", "run", "banana",
        ] {
            match parse_pin(spec) {
                Ok(pin) => {
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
